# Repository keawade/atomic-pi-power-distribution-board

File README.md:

# Atomic Pi power distribution board

KiCAD schematics for a simple power distribution board to distribute power to
up to four Atomic Pi computers with individual power switches for each computer.

## Bill of materials

- 6x 5.08mm pitch screw terminal block connector
- 4x toggle switch for 0.5in hole
- 4x 2x13 2.54mm pitch headers

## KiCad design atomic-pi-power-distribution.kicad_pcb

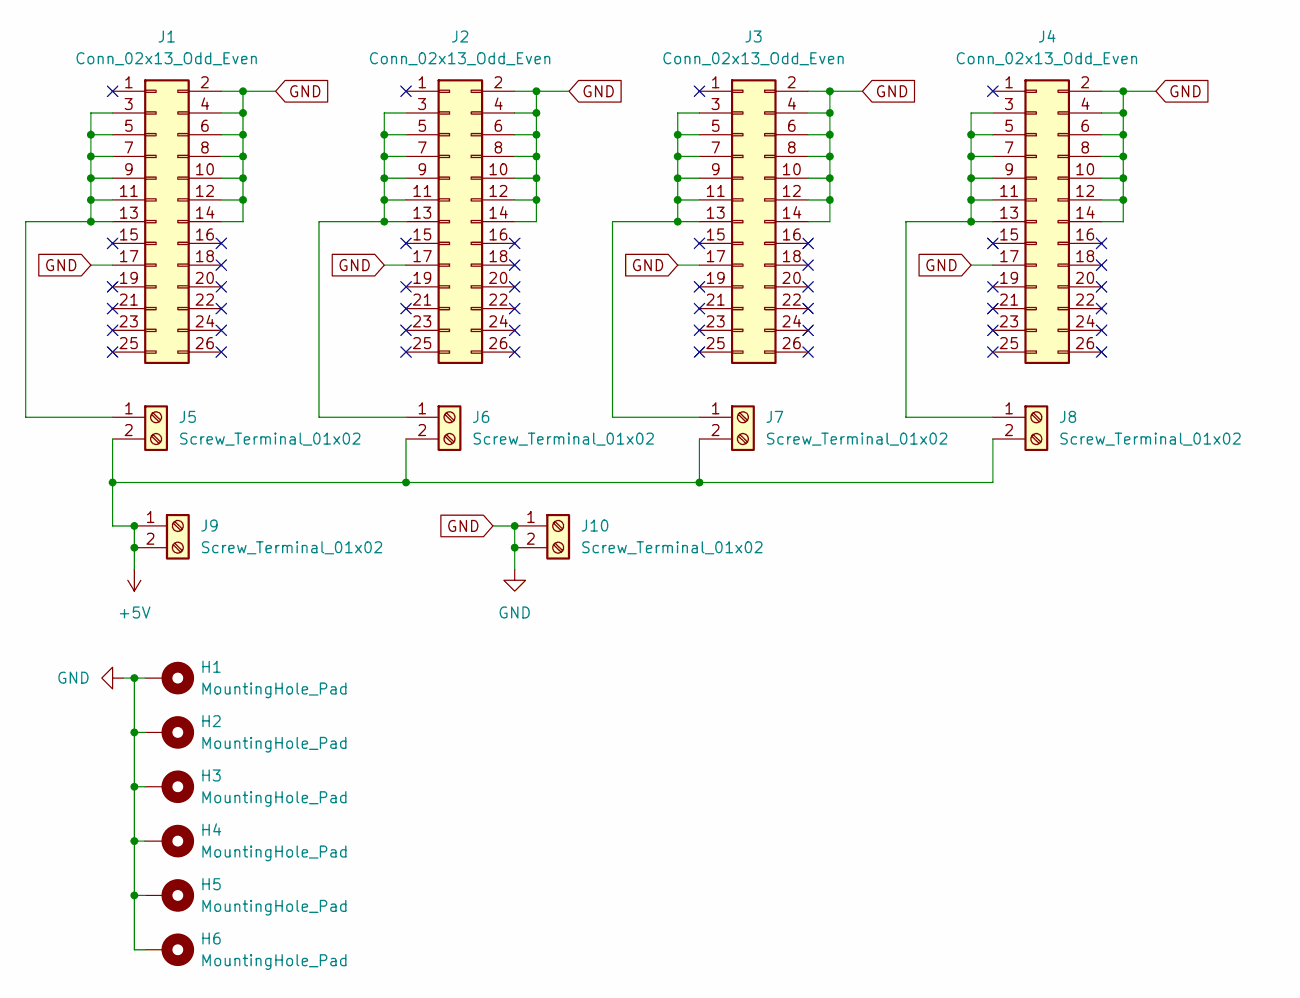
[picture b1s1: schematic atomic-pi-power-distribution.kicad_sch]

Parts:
H1, H2, H3, H4, H5, H6: MountingHole_Pad; MountingHole_3.2mm_M3_Pad_TopBottom
J1, J2, J3, J4: Conn_02x13_Odd_Even; PinHeader_2x13_P2.54mm_Vertical
J5, J6, J7, J8, J9, J10: Screw_Terminal_01x02; TerminalBlock_Altech_AK300-2_P5.00mm

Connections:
+5V: J5.2, J6.2, J7.2, J8.2, J9.1, J9.2
GND: H1.1, H2.1, H3.1, H4.1, H5.1, H6.1, J1.2, J1.4, J1.6, J1.8, J1.10, J1.12, J1.14, J1.17, J2.2, J2.4, J2.6, J2.8, J2.10, J2.12, J2.14, J2.17, J3.2, J3.4, J3.6, J3.8, J3.10, J3.12, J3.14, J3.17, J4.2, J4.4, J4.6, J4.8, J4.10, J4.12, J4.14, J4.17, J10.1, J10.2
unnamed: J1.3, J1.5, J1.7, J1.9, J1.11, J1.13, J5.1
unnamed: J2.3, J2.5, J2.7, J2.9, J2.11, J2.13, J6.1
unnamed: J3.3, J3.5, J3.7, J3.9, J3.11, J3.13, J7.1
unnamed: J4.3, J4.5, J4.7, J4.9, J4.11, J4.13, J8.1

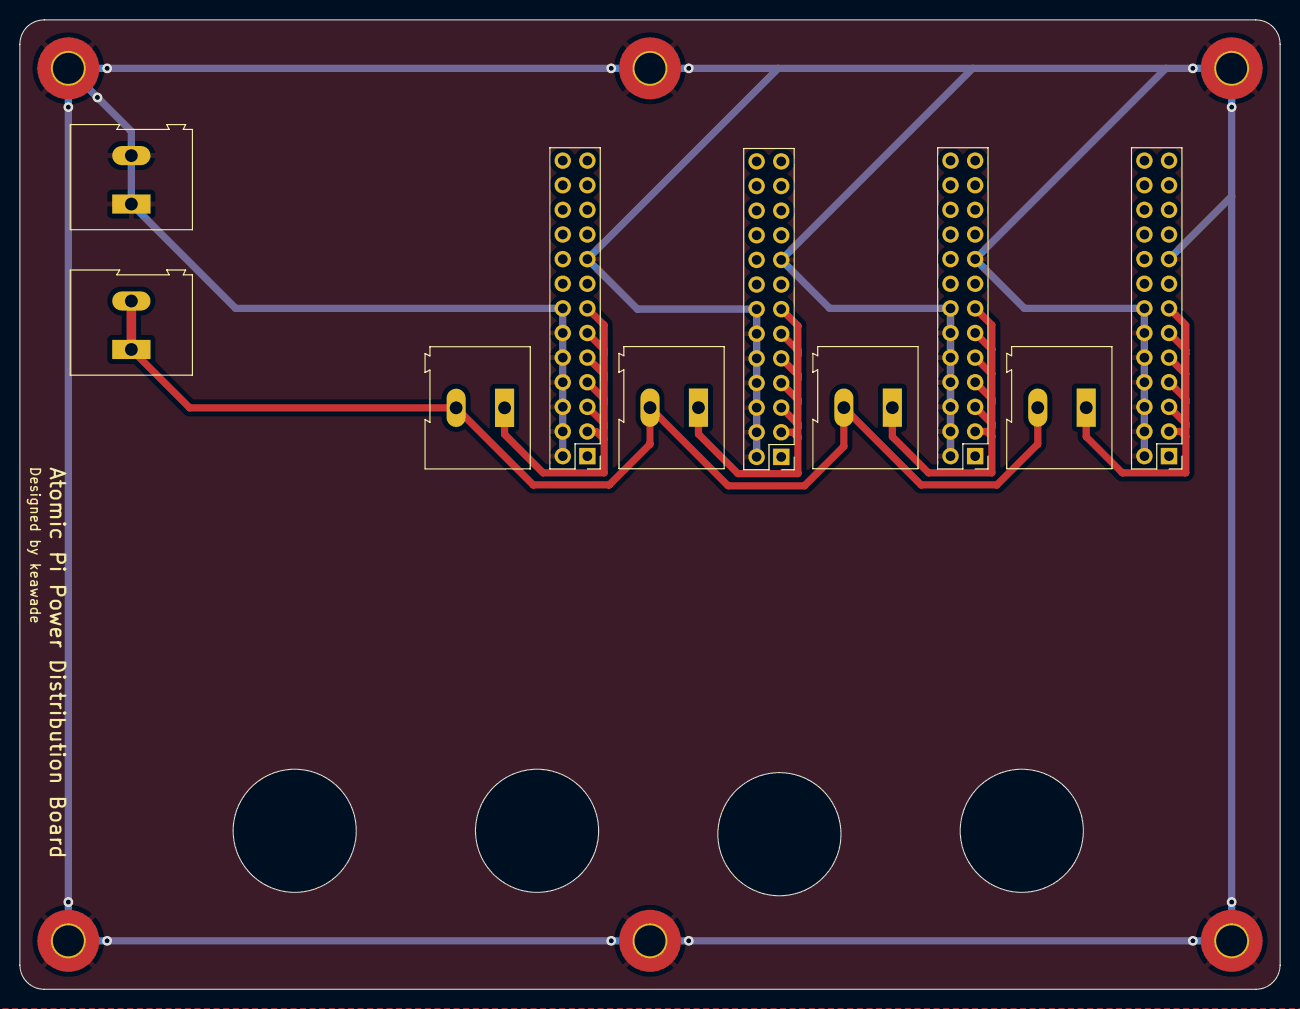
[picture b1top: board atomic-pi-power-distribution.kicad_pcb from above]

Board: 2 copper layers, 130.0 x 100.0 mm, 16 parts (0 on the bottom side), 6 nets.

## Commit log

2023-08-17 Power distribution board rev1
2023-08-17 Ignore KiCAD backups folder
2023-08-17 Add readme with render
2023-08-17 Fix image reference
